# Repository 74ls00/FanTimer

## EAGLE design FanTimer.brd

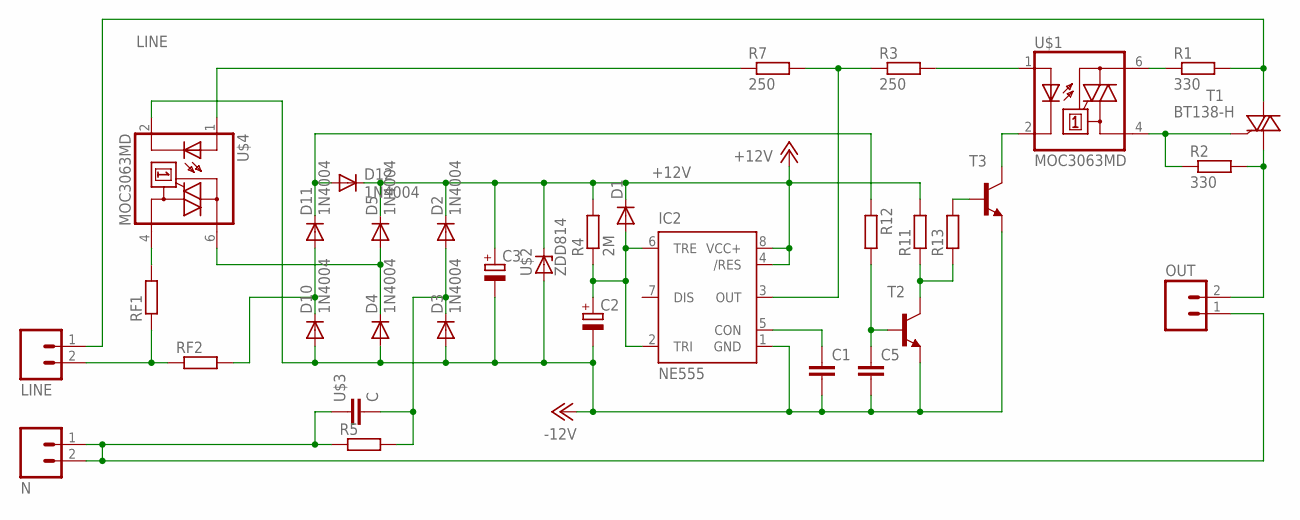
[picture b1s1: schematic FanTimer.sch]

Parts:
C1: C-EU050-025X075; C050-025X075
C2, C3: CPOL-EUE2.5-7; E2,5-7
C5: C-EUC0805; C0805
D1: DIODE-SOD80C; SOD80C
D2, D3, D4, D5, D10, D11, D12: 1N4004; DO41-10
IC2: NE555; DIL-08
LINE: CON_2P; CON_PWR_2PIN4MM
N: CON_2P; CON_PWR_2PIN4MM
OUT: CON_2P; CON_PWR_2PIN4MM
R1, R2: 330; 0207/10
R3, R7: 250; 0207/10
R4: 2M; 0207/10
R5: R-EU_0411/12; 0411/12
R11, R12, R13: R-EU_0207/10; 0207/10
RF1, RF2: R-EU_R1206; R1206
T1: BT138-H; TO220BH
T2, T3: -NPN-TO92-ECB; TO92-ECB
U$1, U$4: MOC3063MD; DIL6
U$2: ZDD814; ZDMETAL
U$3: C; C_22X10

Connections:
+12V: C3.+, D1.C, D2.C, D5.C, D12.C, IC2.4 (/RES), IC2.8 (VCC+), R4.2, R11.2, U$2.C
-12V: C1.2, C2.-, C3.-, C5.2, D3.A, D4.A, D10.A, IC2.1 (GND), T2.E, T3.E, U$2.A, U$4.2 (C)
LINE: LINE.1, R1.2, T1.T2 (A2)
unnamed: D4.C, D5.A, U$4.6 (A2)
unnamed: RF1.2, U$4.4 (A1)
unnamed: C1.1, IC2.5 (CON)
unnamed: R7.1, U$4.1 (A)
unnamed: R2.1, T1.G, U$1.4 (A1)
unnamed: R1.1, U$1.6 (A2)
unnamed: D11.C, D12.A, R12.1
unnamed: C2.+, D1.A, IC2.2 (TRI), IC2.6 (TRE), R4.1
unnamed: OUT.2, R2.2, T1.T1 (A1)
unnamed: IC2.3 (OUT), R3.1, R7.2
unnamed: R3.2, U$1.1 (A)
unnamed: R11.1, R13.1, T2.C
unnamed: LINE.2, RF1.1, RF2.1
unnamed: D2.A, D3.C, R5.2, U$3.2
unnamed: R13.2, T3.B
unnamed: N.1, N.2, OUT.1, R5.1, U$3.1
unnamed: C5.1, R12.2, T2.B
unnamed: T3.C, U$1.2 (C)
SWITCH: D10.C, D11.A, RF2.2

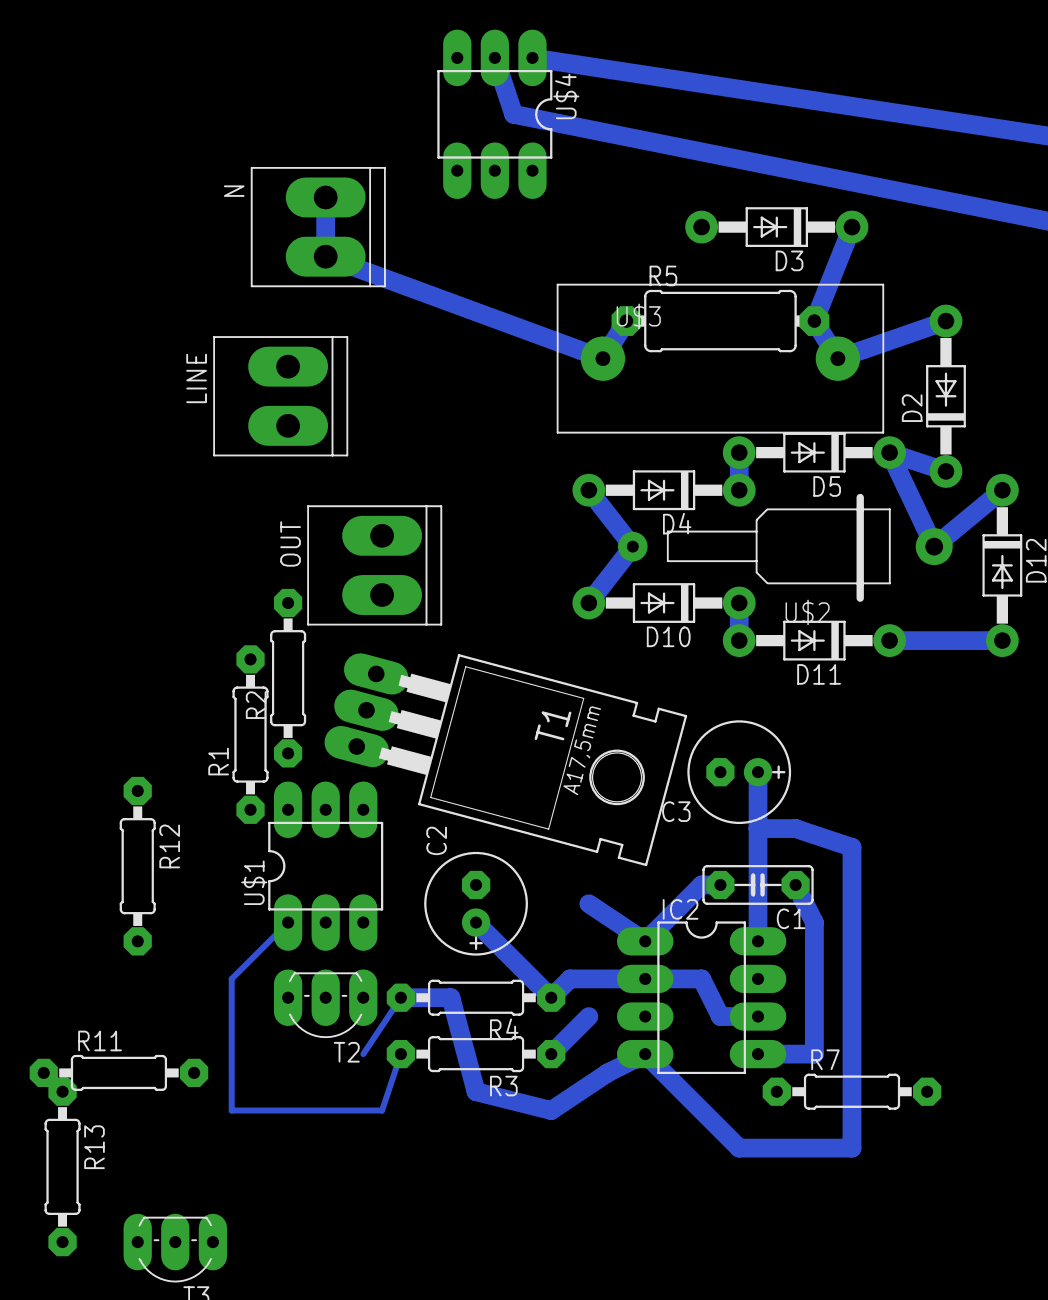
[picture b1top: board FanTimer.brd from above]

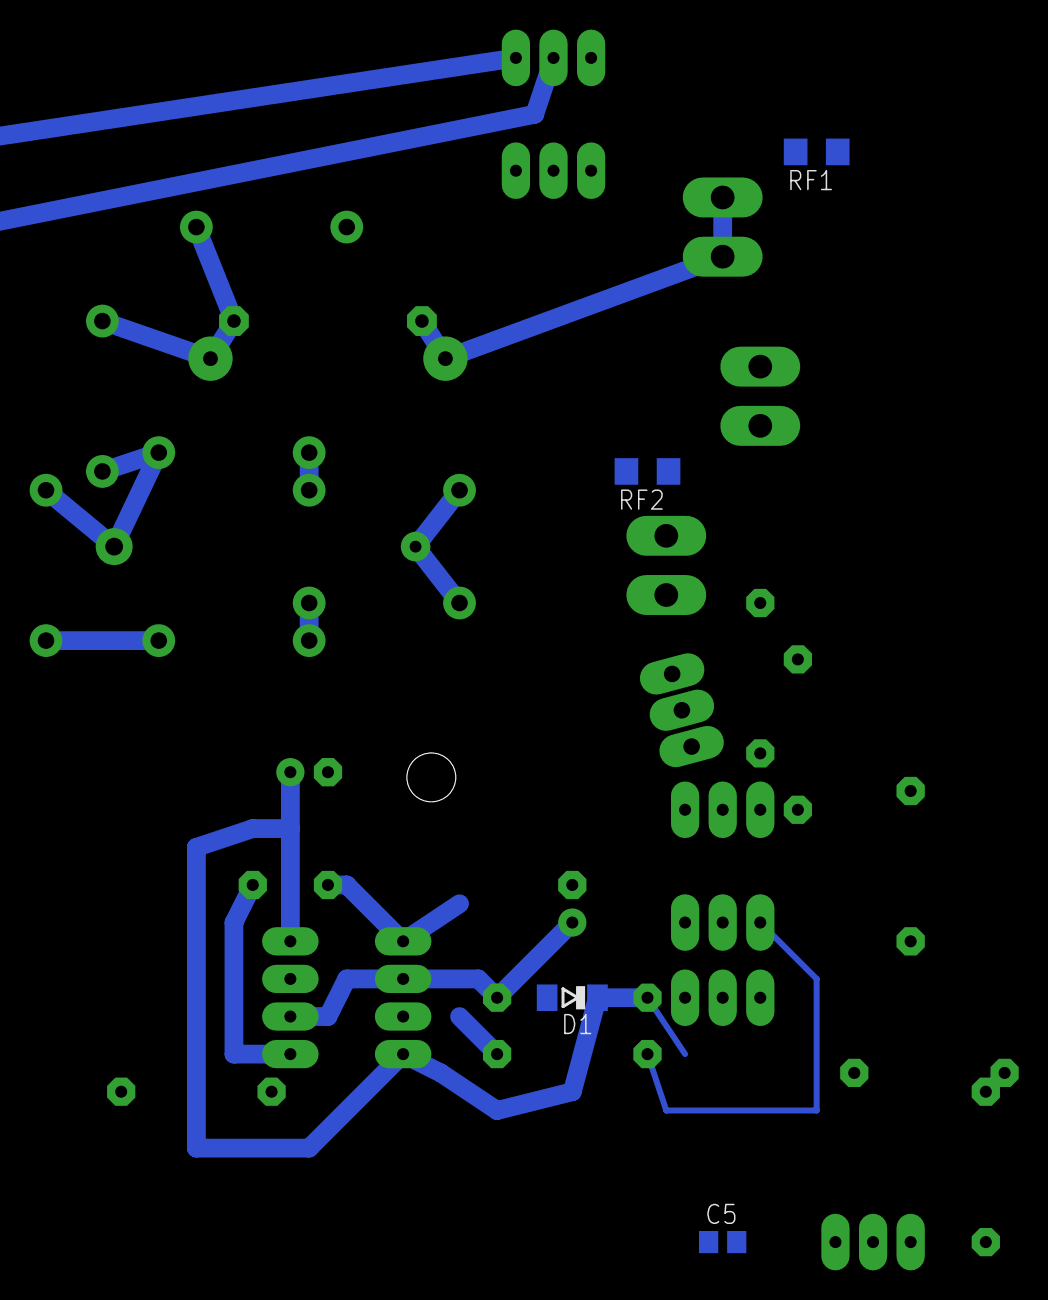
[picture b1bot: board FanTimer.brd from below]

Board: 2 copper layers, 34 parts (4 on the bottom side), 22 nets.

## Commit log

2018-11-27 del 817
